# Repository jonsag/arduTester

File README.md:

# arduTester

An arduino component tester based on [this](https://create.arduino.cc/projecthub/plouc68000/ardutester-v1-13-the-arduino-uno-transistor-tester-dbafb4)

## Prerequisites

>$ sudo apt install make git
>$ sudo apt install avr-libc avrdude gcc-avr subversion  

## Download sources

>$ svn checkout svn://mikrocontroller.net/transistortester  

or

>$ git clone [https://github.com/svn2github/transistortester](https://github.com/svn2github/transistortester)

* Copy the makefile from the folder of this lcd to the default (it may not necessary and can be built in it's original location)

>$ cp transistortester/Software/trunk/ST7735/Makefile transistortester/Software/trunk/default/

* Go to the default directory

>$ cd transistortester/Software/trunk/default

* Edit the Makefile and change the programmer setting

    PROGRAMMER=usbtiny

* Build and upload the code

>$ make
>$ make upload

## Hardware

### ATmega328

Pin no ->  
1 -> Reset  
2 -> D0  
3 -> D1  
4 -> D2 -> LCD pin 14  
5 -> D3 -> LCD pin 13  
6 -> D4 -> LCD pin 12  
7 -> Vcc -> Vcc  
8 -> GND -> GND  
9 -> Crystal  
10 -> Crystal  
11 -> D5 -> LCD pin 11  
12 -> D6 -> LCD pin 6  
13 -> D7 -> LCD pin 4  
14 -> D8 -> TP1 680R  
15 -> D9 -> TP1 470k  
16 -> D10 -> TP2 680R  
17 -> D11 -> TP2 470k  
18 -> D12 -> TP3 680R  
19 -> D13 -> TP3 470k  
20 -> Vcc -> Vcc  
21 -> Aref  
22 -> GND -> GND  
23 -> A0 -> TP1  
24 -> A1 -> TP2  
25 -> A2 -> TP3  
26 -> A3 -> Test button  
27 -> A4  
28 -> A5  

## Atmega-transistor-tester

Atmega-transistor-tester is based on [wagiminator's ATmega-Transistor-Tester](https://github.com/wagiminator/ATmega-Transistor-Tester), which in turn is based on [the original project](https://www.mikrocontroller.net/articles/AVR_Transistortester).  

## Software

Current sources can be found at [Mikrocontroller-net's github page](https://github.com/Mikrocontroller-net/transistortester)

>$ git clone [https://github.com/Mikrocontroller-net/transistortester.git](https://github.com/Mikrocontroller-net/transistortester.git)

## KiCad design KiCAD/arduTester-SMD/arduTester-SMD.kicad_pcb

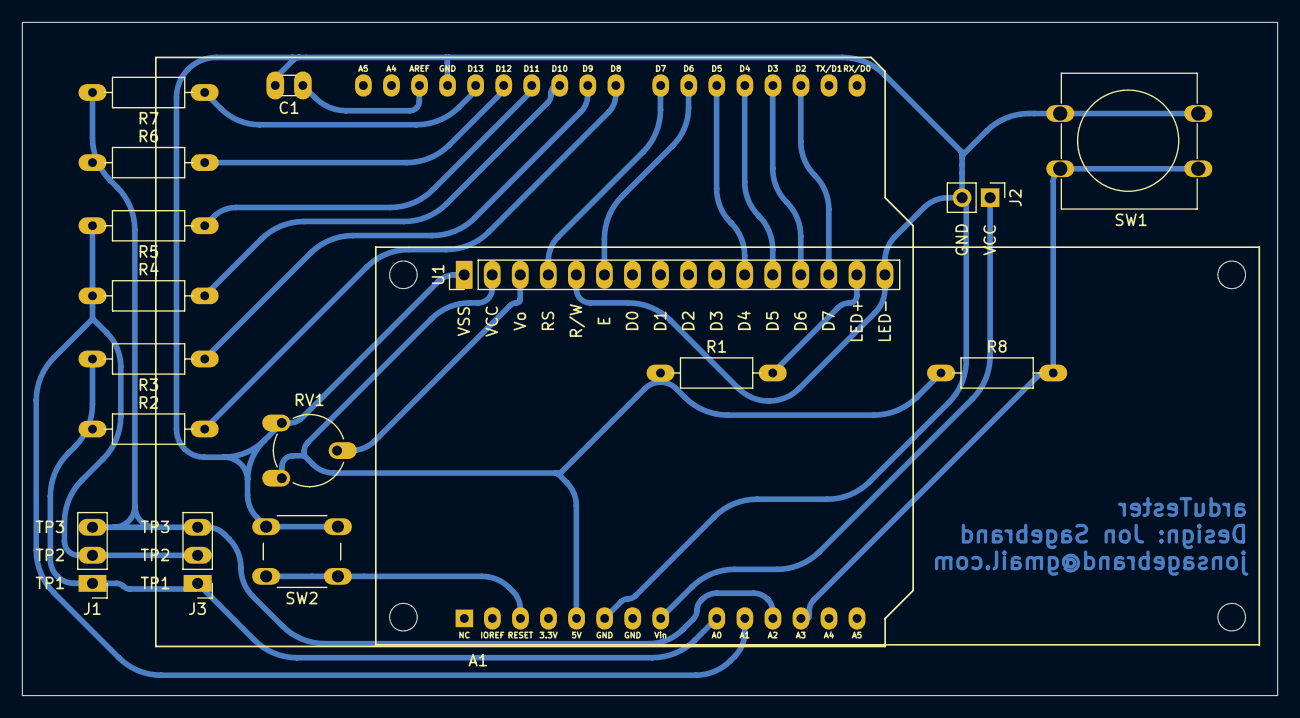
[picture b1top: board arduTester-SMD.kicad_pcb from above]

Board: 2 copper layers, 113.7 x 61.0 mm, 17 parts (0 on the bottom side), 23 nets.

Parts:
A1: Arduino_UNO_R3; Arduino_UNO_R3_shield_large
C1: 1n; C_Disc_D3.0mm_W1.6mm_P2.50mm_larg
J1, J3: 3-pin_test_header; 3-pin_test_header_large
J2: 2-pin_power_input_header
R1: 220R; R_Axial_DIN0207_L6.3mm_D2.5mm_P10.16mm_Horizontal_larger_pa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
R2, R4, R6: 680R; R_Axial_DIN0207_L6.3mm_D2.5mm_P10.16mm_Horizontal_larger_pa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
R3, R5, R7: 470k; R_Axial_DIN0207_L6.3mm_D2.5mm_P10.16mm_Horizontal_larger_pa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
R8: 10k; R_Axial_DIN0207_L6.3mm_D2.5mm_P10.16mm_Horizontal_larger_pa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
RV1: 10k; Potentiometer_Piher_PT-6-V_Vertical_larger_pads
SW1: SW_Push; SW_PUSH-12mm_large
SW2: SW_Push; SW_PUSH_6mm_large
U1: LCD_HD44780; LCD_HD44780_16x2_w_headers_large

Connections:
+5V: A1.5 (+5V), R1.1, R8.1, RV1.1, U1.2 (VDD)
GND: A1.6 (GND), A1.7 (GND), A1.29 (GND), C1.2, J2.2 (GND), RV1.3, SW1.2, SW2.2, U1.1 (VSS), U1.5 (R/W), U1.16 (LED-)
unnamed: A1.3 (~RESET), SW2.1
unnamed: A1.8 (VIN), J2.1 (VCC)
unnamed: A1.12 (A3), R8.2, SW1.1
unnamed: A1.17 (D2), U1.14 (DB7)
unnamed: A1.18 (D3), U1.13 (DB6)
unnamed: A1.19 (D4), U1.12 (DB5)
unnamed: A1.20 (D5), U1.11 (DB4)
unnamed: A1.21 (D6), U1.6 (E)
unnamed: A1.22 (D7), U1.4 (RS)
unnamed: A1.23 (D8), R2.2
unnamed: A1.24 (D9), R3.1
unnamed: A1.25 (D10), R4.2
unnamed: A1.26 (D11), R5.1
unnamed: A1.27 (D12), R6.2
unnamed: A1.28 (D13), R7.1
unnamed: A1.30 (AREF), C1.1
unnamed: R1.2, U1.15 (LED+)
unnamed: RV1.2, U1.3 (VO)
TP1: A1.9 (A0), J1.1 (TP1), J3.1 (TP1), R2.1, R3.2
TP2: A1.10 (A1), J1.2 (TP2), J3.2 (TP2), R4.1, R5.2
TP3: A1.11 (A2), J1.3 (TP3), J3.3 (TP3), R6.1, R7.2

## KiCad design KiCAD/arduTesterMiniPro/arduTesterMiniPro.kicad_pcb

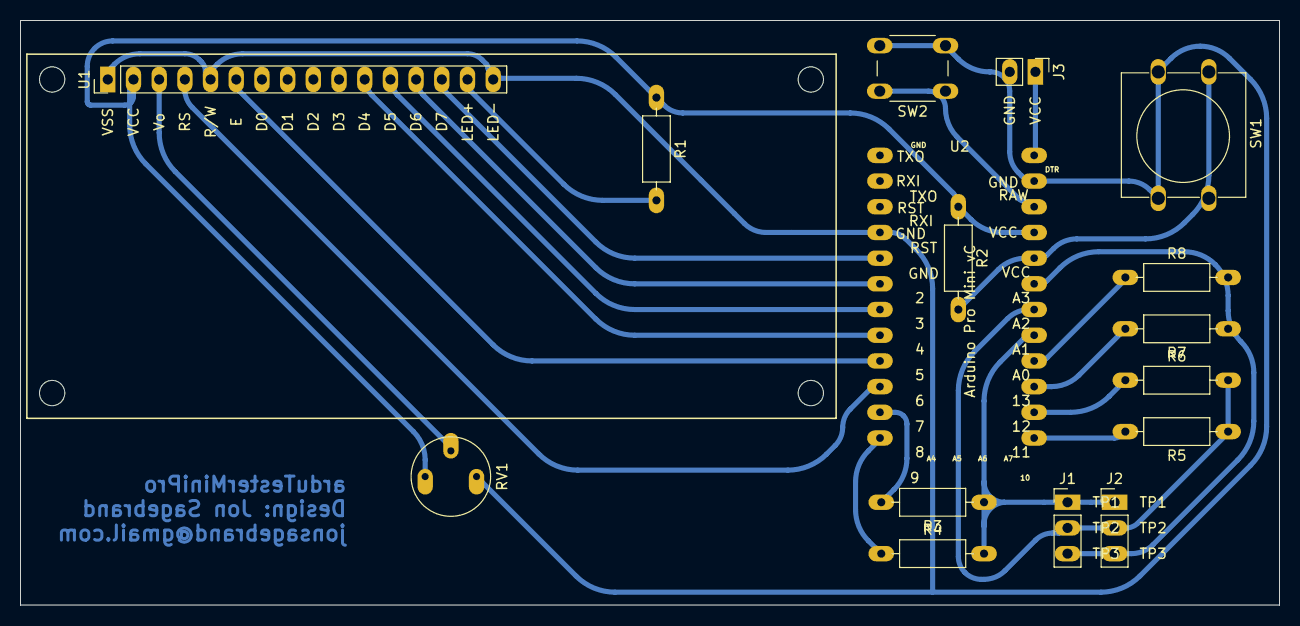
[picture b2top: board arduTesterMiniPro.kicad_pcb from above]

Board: 2 copper layers, 124.5 x 57.8 mm, 16 parts (0 on the bottom side), 22 nets.

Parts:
J1, J2: 3-pin_test_header; 3-pin_test_header_large
J3: 2-pin_power_input_header; 2-pin_power_input_header_larger_pads
R1: 220R; R_Axial_DIN0207_L6.3mm_D2.5mm_P10.16mm_Horizontal_larger_pa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
R2: 10k; R_Axial_DIN0207_L6.3mm_D2.5mm_P10.16mm_Horizontal_larger_pa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
R3, R5, R7: 680R; R_Axial_DIN0207_L6.3mm_D2.5mm_P10.16mm_Horizontal_larger_pa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
R4, R6, R8: 470k; R_Axial_DIN0207_L6.3mm_D2.5mm_P10.16mm_Horizontal_larger_pa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
RV1: 10k; Potentiometer_Bourns_3339P_Vertical_large
SW1: SW_Push; SW_PUSH-12mm_large
SW2: SW_Push; SW_PUSH_6mm_large
U1: LCD_HD44780; LCD_HD44780_16x2_w_headers_large
U2: Arduino_Mini_Pro; Arduino_Pro_Mini_vC_only_sides_larger_pads

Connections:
+5V: R1.1, R2.1, RV1.1, U1.2 (VDD), U2.16 (VCC)
GND: J3.2 (GND), RV1.3, SW1.2, SW2.2, U1.1 (VSS), U1.5 (R/W), U1.16 (LED-), U2.4 (GND), U2.14 (GND)
unnamed: J3.1 (VCC), U2.13 (RAW)
unnamed: R1.2, U1.15 (LED+)
unnamed: R2.2, SW1.1, U2.17 (A3)
unnamed: R3.2, U2.11 (8)
unnamed: R4.1, U2.12 (9)
unnamed: R5.2, U2.24 (10)
unnamed: R6.1, U2.23 (11)
unnamed: R7.2, U2.22 (12)
unnamed: R8.1, U2.21 (13)
unnamed: RV1.2, U1.3 (VO)
unnamed: SW2.1, U2.15 (RST)
unnamed: U1.4 (RS), U2.10 (7)
unnamed: U1.6 (E), U2.9 (6)
unnamed: U1.11 (DB4), U2.8 (5)
unnamed: U1.12 (DB5), U2.7 (4)
unnamed: U1.13 (DB6), U2.6 (3)
unnamed: U1.14 (DB7), U2.5 (2)
TP1: J1.1 (TP1), J2.1 (TP1), R3.1, R4.2, U2.20 (A0)
TP2: J1.2 (TP2), J2.2 (TP2), R5.1, R6.2, U2.19 (A1)
TP3: J1.3 (TP3), J2.3 (TP3), R7.1, R8.2, U2.18 (A2)

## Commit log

2021-02-07 forgot resistor
2021-02-08 mini pro
2021-02-09 Schematics and PCB. Scad
2021-02-09 schematics
2021-02-10 readme
2021-02-18 set resistor values
2021-02-18 button
2022-05-13 kicad6
2025-03-31 kicad version
2025-03-31 a start on a new transistor tester, SMD
